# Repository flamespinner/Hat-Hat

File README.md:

# Hat-Hat

### Point of this Project

### Fair Use

###

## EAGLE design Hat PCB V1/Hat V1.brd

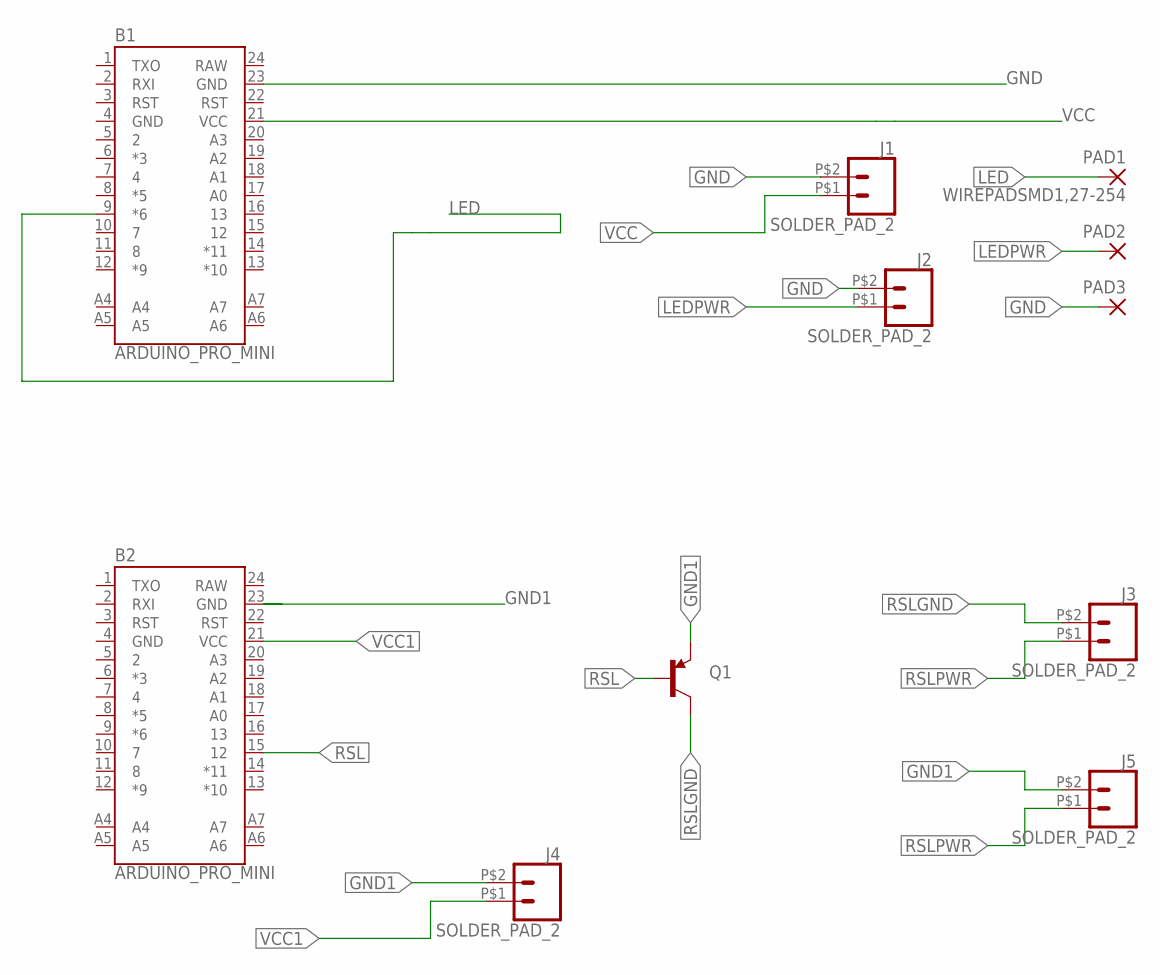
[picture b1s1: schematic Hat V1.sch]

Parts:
B1, B2: ARDUINO_PRO_MINI
J1, J2, J3, J4, J5: SOLDER_PAD_2
PAD1: WIREPADSMD1,27-254; SMD1,27-2,54
PAD2, PAD3: SMD2; SMD1,27-2,54
Q1: TRANSISTOR_PNPSMD-2; SOT89

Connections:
GND: B1.4 (GND), B1.23 (GND), B2.4 (GND), J1.P$2 (2), J2.P$2 (2), PAD3.1
GND1: B2.23 (GND), J4.P$2 (2), J5.P$2 (2), Q1.3 (E)
LED: B1.9 (*6), PAD1.1
LEDPWR: J2.P$1 (1), PAD2.1
RAW: B1.24 (RAW), B2.24 (RAW)
RSL: B2.15 (12), Q1.1 (B)
RSLGND: J3.P$2 (2), Q1.2 (C)
RSLPWR: J3.P$1 (1), J5.P$1 (1)
VCC: B1.21 (VCC), J1.P$1 (1)
VCC1: B2.21 (VCC), J4.P$1 (1)

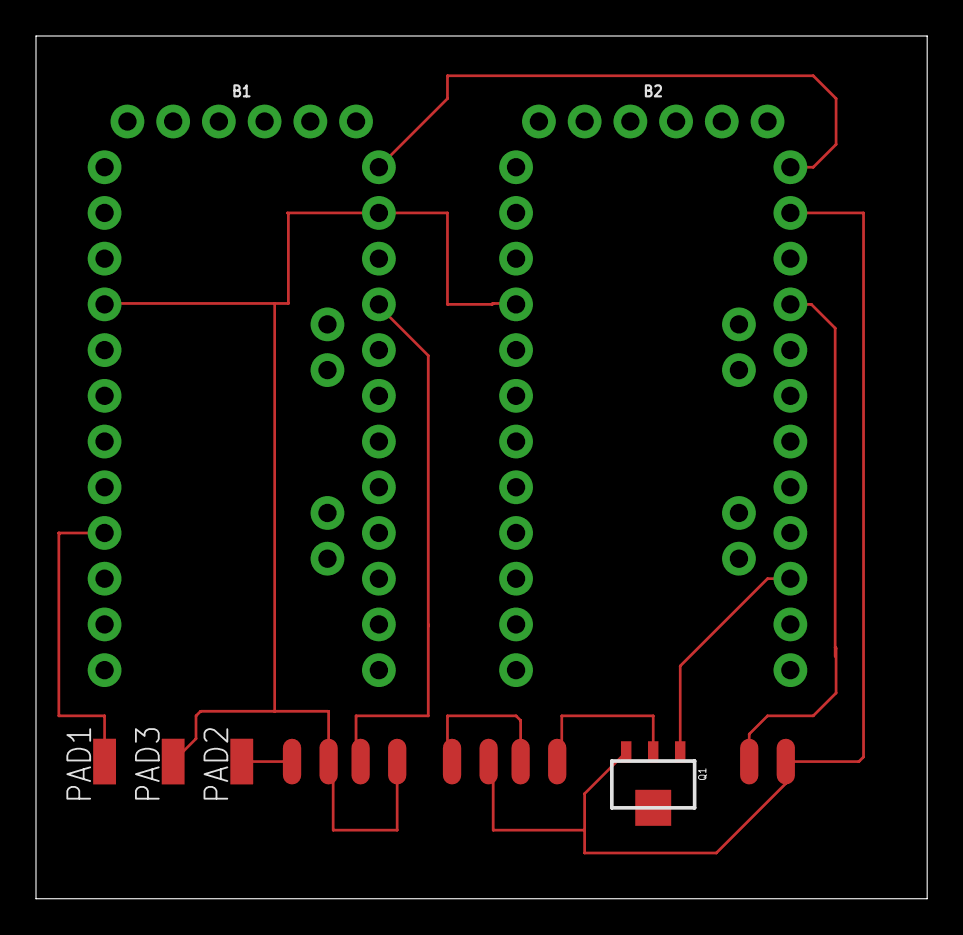
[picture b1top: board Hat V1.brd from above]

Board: 2 copper layers, 49.5 x 47.9 mm, 11 parts (0 on the bottom side), 10 nets.

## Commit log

2018-04-09 RSL Blink Arduino
2018-04-09 Added Transister Doc
2018-04-29 HAT HAT LED TEST
2019-03-25 Added Hat.py
2019-03-25 hat.py
2019-03-25 Added Text for This year
2019-03-25 Added Gen 1 RSL Code
2019-03-27 Removed Pi code as it is not supported by Circuit python
2019-03-27 Added to git Ignore
2019-03-27 Added Libraries
2019-03-29 updated Git Itnore
2019-03-29 Added neo pixel docs
2019-03-30 Moved Old copy of code, and modified. WOrks now
2019-03-30 Added a Sanity Check
2019-04-20 Removed some text, and added RSL
2019-04-22 Uploaded a backup copy of the last working code
2019-04-28 Reverted to Working Code.
2019-04-28 Code Fixes. Compiles now
2019-04-28 Removed LED Def
2020-03-07 Hat PCB
2020-03-16 Updated Sketches for 2020

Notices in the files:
parts and their libraries:
SparkFun-Boards: Licensing: Creative Commons ShareAlike 4.0 International - https://creativecommons.org/licenses/by-sa/4.0
